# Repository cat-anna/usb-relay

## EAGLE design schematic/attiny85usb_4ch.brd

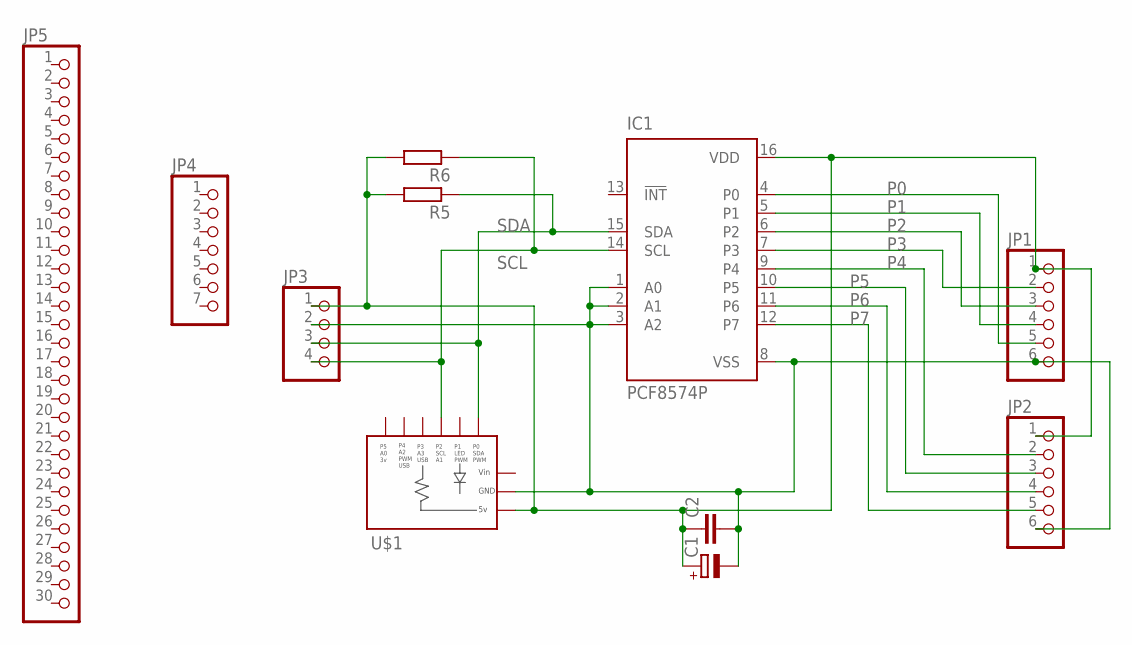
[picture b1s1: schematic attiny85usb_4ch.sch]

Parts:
C1: CPOL-EUE2-5; E2-5
C2: C-EU025-050X050; C025-050X050
IC1: PCF8574P; DIL16
JP1: PINHD-1X6; 1X06
JP2: PINHD-1X6/90; 1X06/90
JP3: PINHD-1X4/90; 1X04/90
JP4: PINHD-1X7; 1X07
JP5: PINHD-1X30; 1X30
R5, R6: R-EU_0207/10; 0207/10
U$1: DIGISPARK

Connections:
GND: C1.-, C2.2, IC1.1 (A0), IC1.2 (A1), IC1.3 (A2), IC1.8 (VSS), JP1.6, JP2.6, JP3.2, U$1.GND
P0: IC1.4 (P0), JP1.5
P1: IC1.5 (P1), JP1.4
P2: IC1.6 (P2), JP1.3
P3: IC1.7 (P3), JP1.2
P4: IC1.9 (P4), JP2.2
P5: IC1.10 (P5), JP2.3
P6: IC1.11 (P6), JP2.4
P7: IC1.12 (P7), JP2.5
SCL: IC1.14 (SCL), JP3.4, R6.1, U$1.P2
SDA: IC1.15 (SDA), JP3.3, R5.1, U$1.P0
VCC: C1.+, C2.1, IC1.16 (VDD), JP1.1, JP2.1, JP3.1, R5.2, R6.2, U$1.5V
VIN: U$1.VIN

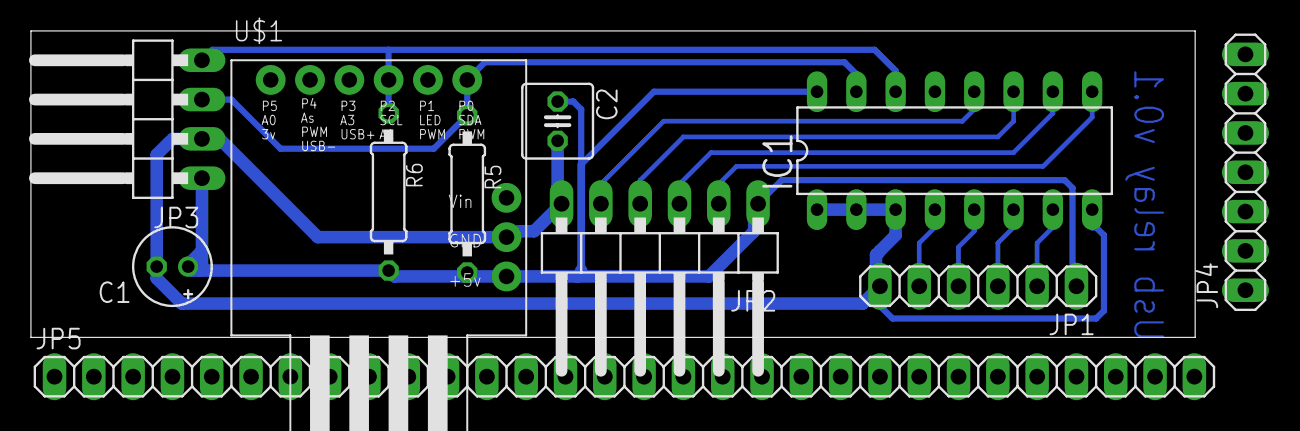
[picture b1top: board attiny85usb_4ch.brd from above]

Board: 2 copper layers, 75.2 x 19.8 mm, 11 parts (0 on the bottom side), 12 nets.

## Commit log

2020-08-01 initial release
2020-11-13 update schematic
2020-11-13 add ping command and activity led
2020-11-15 add micronucleus bootloader
2020-11-15 add rules for udev
